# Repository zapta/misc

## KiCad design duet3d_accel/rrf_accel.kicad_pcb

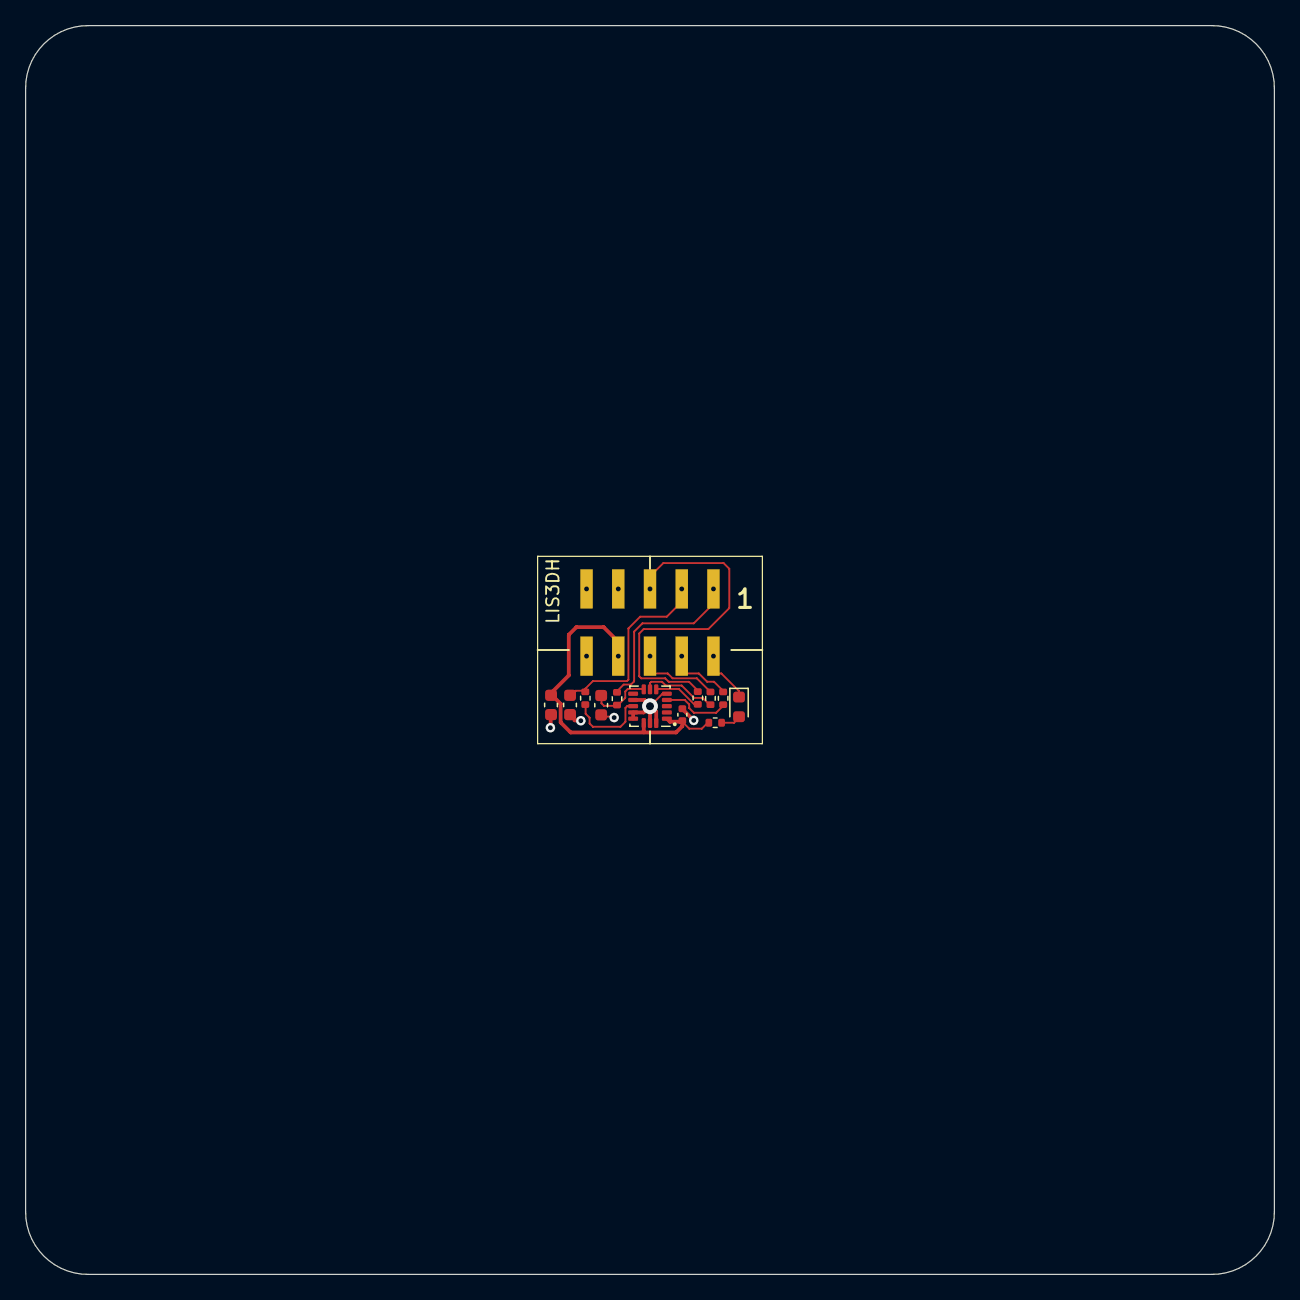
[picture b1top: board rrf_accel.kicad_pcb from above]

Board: 2 copper layers, 100.0 x 100.0 mm, 13 parts (0 on the bottom side), 13 nets.

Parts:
C1: 10uf; C_0603_1608Metric
C2: 100n; C_0402_1005Metric
C3, C4: 470pf; C_0603_1608Metric
D1: LED; LED_0603_1608Metric
J1: Conn_02x05_Odd_Even; PinHeader_2x05_P2.54mm_Vertical_SMD
R1, R2, R4, R5, R6: 62R; R_0402_1005Metric
R3: 220R; R_0402_1005Metric
U1: LIS3DH; LGA-16_3x3mm_P0.5mm_LayoutBorder3x5y

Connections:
+3V3: C1.1, C2.1, J1.8, R3.1, U1.1 (VDD_IO), U1.14 (VDD)
/CS: J1.1, R6.1
/INT: C3.1, J1.3, R1.1
/MISO: J1.6, R2.1
/MOSI: J1.5, R4.1
/SCK: J1.4, R5.1
GNDD: C1.2, C2.2, C3.2, C4.2, D1.1 (K), J1.2, U1.5 (GND), U1.10 (GND), U1.12 (GND), U1.13 (ADC3), U1.15 (ADC2), U1.16 (ADC1)
unnamed: D1.2 (A), R3.2
unnamed: C4.1, R6.2, U1.8 (CS)
unnamed: R1.2, U1.11 (INT1)
unnamed: R5.2, U1.4 (SCL/SPC)
unnamed: R4.2, U1.6 (SDA/SDI/SDO)
unnamed: R2.2, U1.7 (SDO/SA0)

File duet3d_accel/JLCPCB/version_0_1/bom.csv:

Designator,Footprint,Quantity,Value,LCSC Part #
C1,0603,1,10uf,C96446
C2,0402,1,100n,C1525
"C3, C4",0603,2,470pf,C1620
D1,0603,1,LED,C72043
J1,PinHeader_2x05_P2.54mm_Vertical_SMD,1,Conn_02x05_Odd_Even,C3294463
"R1, R2, R4, R5, R6",0402,5,62R,C25120
R3,0402,1,220R,C25091
U1,LGA-16_3x3mm_P0.5mm_LayoutBorder3x5y,1,LIS3DH,C15134

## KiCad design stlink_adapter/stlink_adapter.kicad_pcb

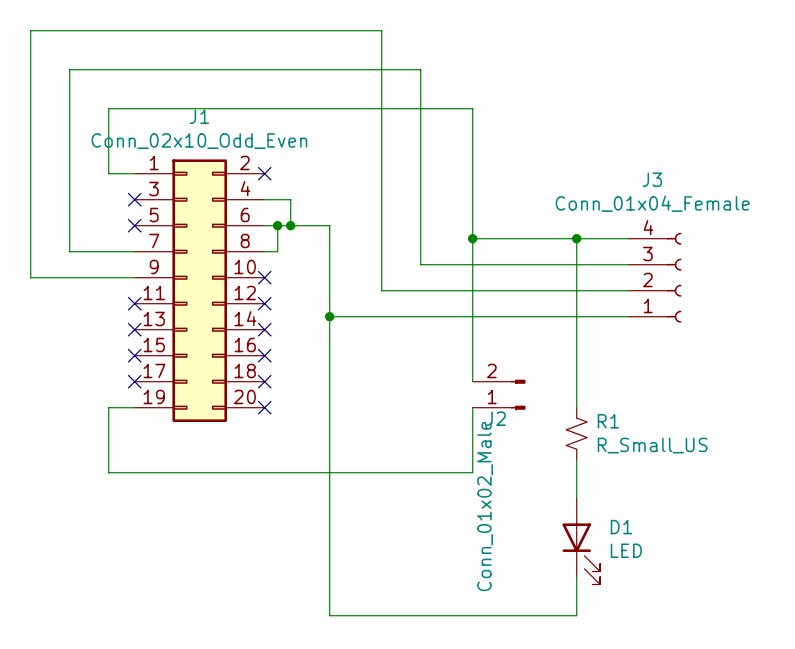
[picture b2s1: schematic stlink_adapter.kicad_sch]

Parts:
D1: LED; LED_0603_1608Metric_Pad1.05x0.95mm_HandSolder
J1: Conn_02x10_Odd_Even; PinHeader_2x10_P2.54mm_Vertical
J2: Conn_01x02_Male; PinHeader_1x02_P2.54mm_Vertical
J3: Conn_01x04_Female; PinHeader_1x04_P2.54mm_Vertical
R1: R_Small_US; R_0603_1608Metric_Pad1.05x0.95mm_HandSolder

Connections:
unnamed: D1.2 (A), R1.2
unnamed: D1.1 (K), J1.4, J1.6, J1.8, J3.1
unnamed: J1.1, J2.2, J3.4, R1.1
unnamed: J1.7, J3.3
unnamed: J1.9, J3.2
unnamed: J1.19, J2.1

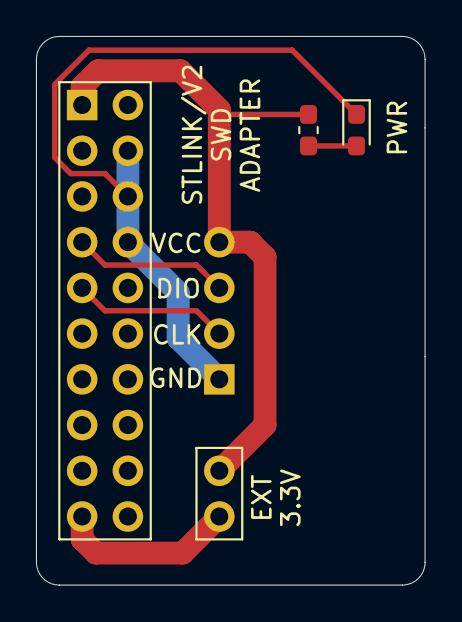
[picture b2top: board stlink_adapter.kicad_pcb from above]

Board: 2 copper layers, 21.6 x 30.5 mm, 5 parts (0 on the bottom side), 6 nets.

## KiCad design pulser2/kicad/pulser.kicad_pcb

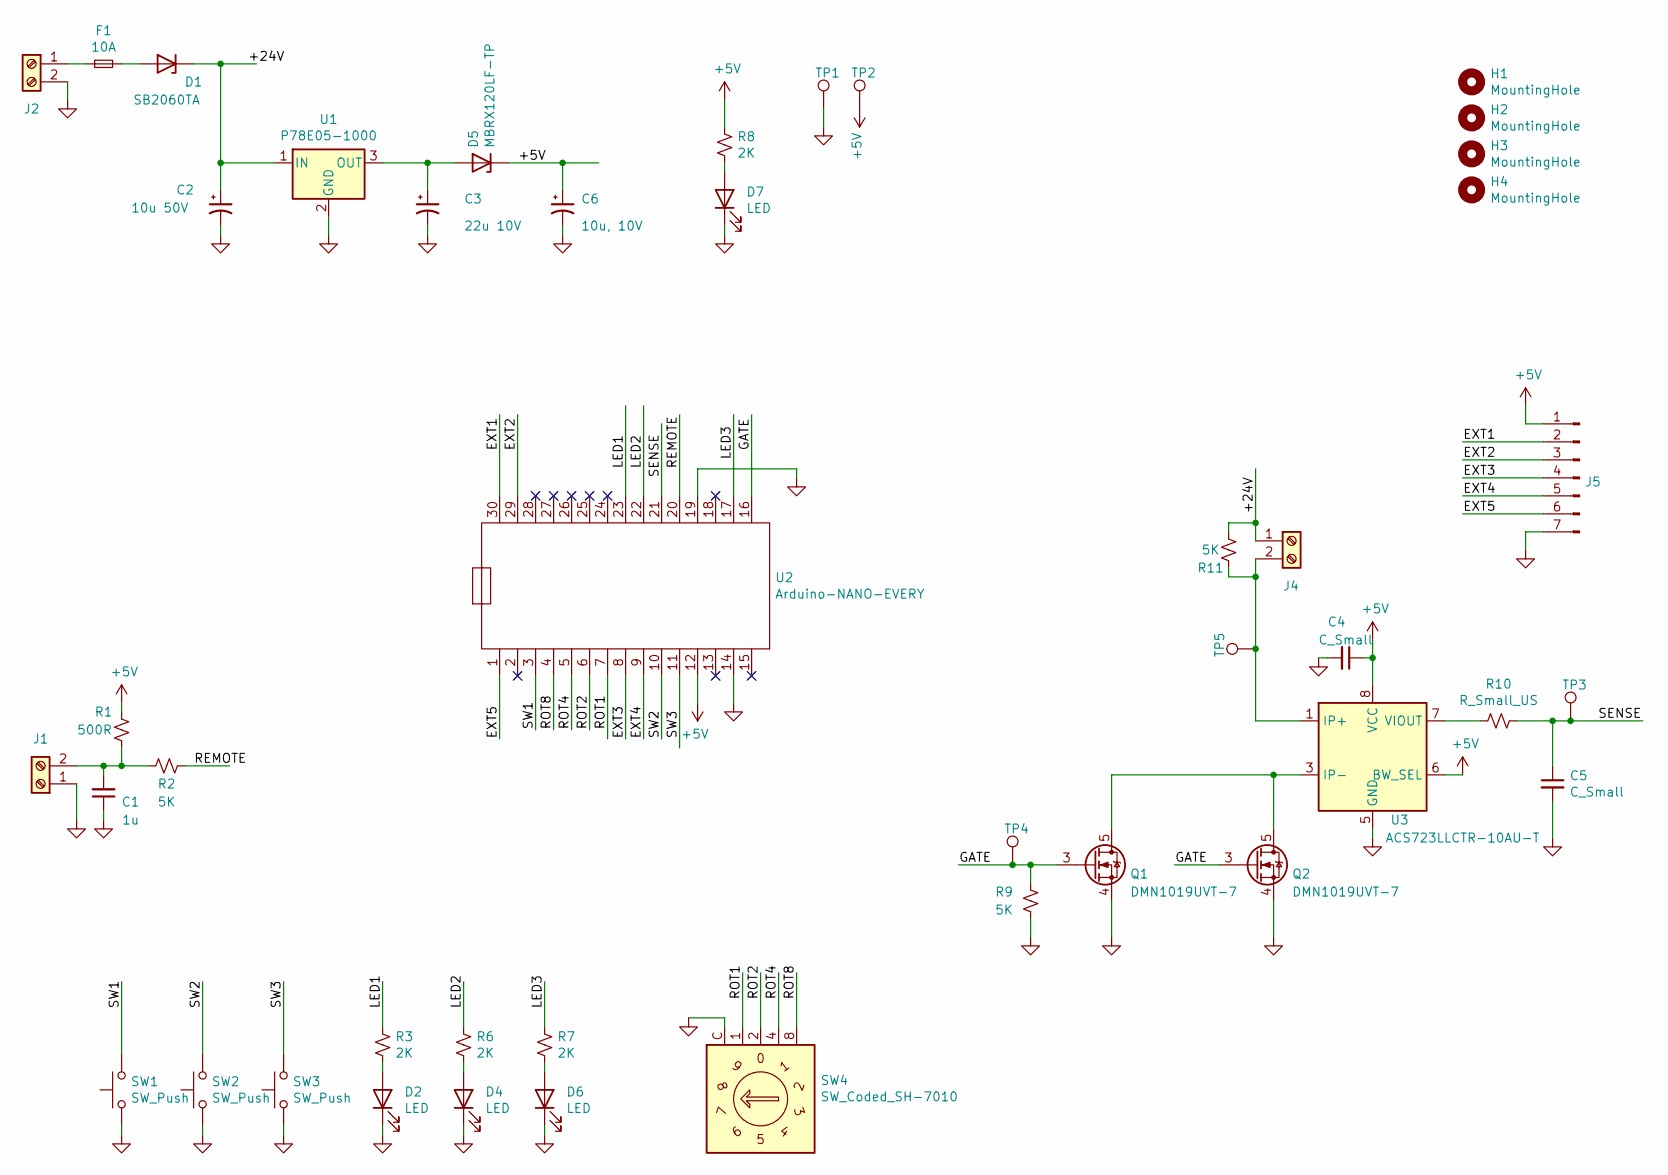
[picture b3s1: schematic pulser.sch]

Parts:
C1: 1u; C_0603_1608Metric
C2: 10u 50V; CP_Radial_D8.0mm_P2.50mm
C3: 22u 10V; CP_Radial_D5.0mm_P2.00mm
C4, C5: C_Small; C_0603_1608Metric
C6: 10u, 10V; C_1206_3216Metric_Pad1.42x1.75mm_HandSolder
D1: SB2060TA; D_DO-201AD_P12.70mm_Horizontal
D2, D4, D6, D7: LED; LED_0603_1608Metric
D5: MBRX120LF-TP; D_SOD-123
F1: 10A; Fuse_Blade_Mini_directSolder
H1, H2, H3, H4: MountingHole
J1: Screw_Terminal_01x02; TERMINAL_SMALL
J2, J4: Screw_Terminal_01x02; TerminalBlock_bornier-2_P5.08mm
J5: Conn_01x07_Male; Molex_KK-254_AE-6410-07A_1x07_P2.54mm_Vertical
Q1, Q2: DMN1019UVT-7; SOT-23-6_Handsoldering
R1: 500R; R_0603_1608Metric
R2, R9, R11: 5K; R_0603_1608Metric
R3, R6, R7, R8: 2K; R_0603_1608Metric
R10: R_Small_US; R_0603_1608Metric
SW1, SW2, SW3: SW_Push; SW_PUSH_6mm
SW4: SW_Coded_SH-7010; ROTARY2
TP1, TP2, TP3, TP4, TP5: TestPoint; Testpoint
U1: P78E05-1000; DC_DC
U2: Arduino-NANO-EVERY; NANO_33_Socket_Castell
U3: ACS723LLCTR-10AU-T; SOIC-8_3.9x4.9mm_P1.27mm

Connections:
+5V: C4.1, C6.1, D5.1 (K), J5.1, R1.2, R8.1, TP2.1, U2.12, U3.6 (BW_SEL), U3.8 (VCC)
/+24V: C2.1, D1.1 (K), J4.1, R11.2, U1.1 (IN)
/EXT1: J5.2, U2.30
/EXT2: J5.3, U2.29
/EXT3: J5.4, U2.8
/EXT4: J5.5, U2.9
/EXT5: J5.6, U2.1
/GATE: Q1.3 (G), Q2.3 (G), R9.2, TP4.1, U2.16
/LED1: R3.1, U2.23
/LED2: R6.1, U2.22
/LED3: R7.1, U2.17
/REMOTE: R2.2, U2.20
/ROT1: SW4.1, U2.7
/ROT2: SW4.2, U2.6
/ROT4: SW4.4, U2.5
/ROT8: SW4.8, U2.4
/SENSE: C5.1, R10.1, TP3.1, U2.21
/SW1: SW1.2, U2.3
/SW2: SW2.2, U2.10
/SW3: SW3.2, U2.11
GND: C1.1, C2.2, C3.2, C4.2, C5.2, C6.2, D2.1 (K), D4.1 (K), D6.1 (K), D7.1 (K), J1.1, J2.2, J5.7, Q1.4 (S), Q2.4 (S), R9.1, SW1.1, SW2.1, SW3.1, SW4.C, TP1.1, U1.2 (GND), U2.14, U2.19, U3.5 (GND)
unnamed: C1.2, J1.2, R1.1, R2.1
unnamed: C3.1, D5.2 (A), U1.3 (OUT)
unnamed: D1.2 (A), F1.2
unnamed: D2.2 (A), R3.2
unnamed: D4.2 (A), R6.2
unnamed: D6.2 (A), R7.2
unnamed: D7.2 (A), R8.2
unnamed: F1.1, J2.1
unnamed: J4.2, R11.1, TP5.1, U3.1 (IP+), U3.2 (IP+)
unnamed: Q1.1 (D), Q1.2 (D), Q1.5 (D), Q1.6 (D), Q2.1 (D), Q2.2 (D), Q2.5 (D), Q2.6 (D), U3.3 (IP-), U3.4 (IP-)
unnamed: R10.2, U3.7 (VIOUT)

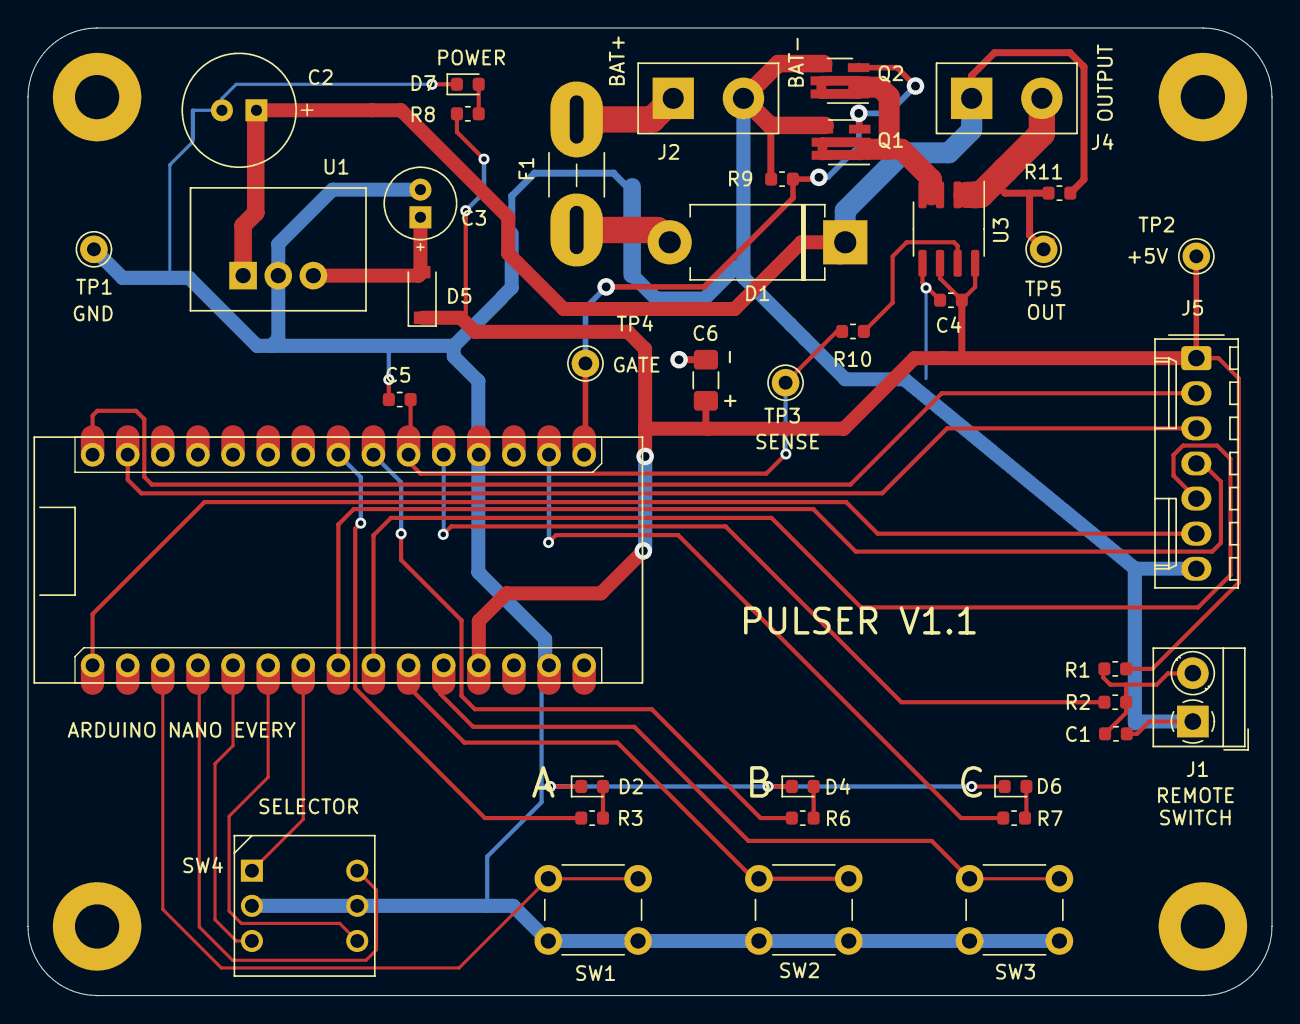
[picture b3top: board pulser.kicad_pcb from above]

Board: 2 copper layers, 90.0 x 70.0 mm, 44 parts (0 on the bottom side), 32 nets.

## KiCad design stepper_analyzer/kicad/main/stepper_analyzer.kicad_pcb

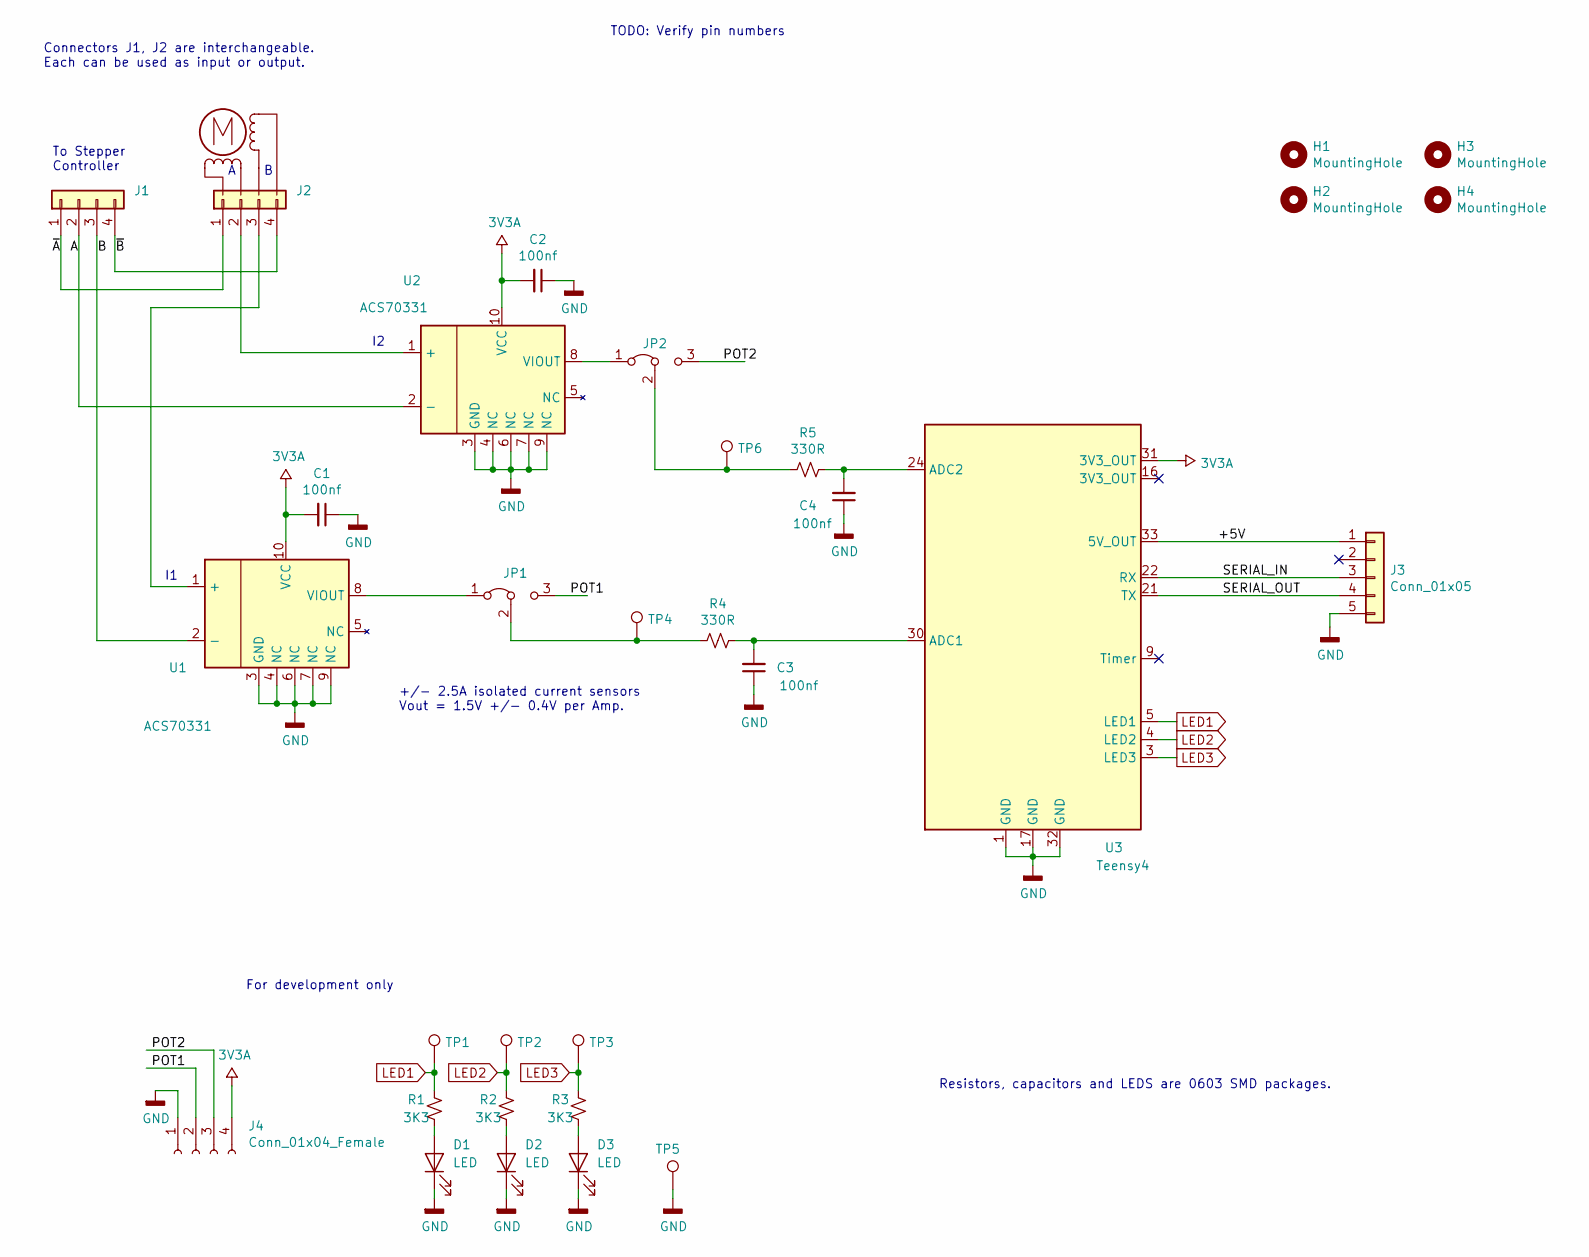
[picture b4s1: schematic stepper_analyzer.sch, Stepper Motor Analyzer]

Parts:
C1, C2, C3, C4: 100nf; C_0603_1608Metric
D1, D2, D3: LED; LED_0603_1608Metric
H1, H2, H3, H4: MountingHole; MountingHole_3.2mm_M3_Pad
J1, J2: Conn_01x04; Molex_KK-254_AE-6410-04A_1x04_P2.54mm_Vertical
J3: Conn_01x05; Molex_KK-254_AE-6410-05A_1x05_P2.54mm_Vertical
J4: Conn_01x04_Female; PinHeader_1x04_P2.54mm_Vertical
JP1, JP2: Jumper_3_Bridged12; PinHeader_1x03_P2.54mm_Vertical
M1: Stepper_Motor_bipolar
R1, R2, R3: 3K3; R_0603_1608Metric
R4, R5: 330R; R_0603_1608Metric
TP1, TP2, TP3, TP4, TP5, TP6: TestPoint; TestPoint_Loop_D1.80mm_Drill1.0mm_Beaded
U1, U2: ACS70331; Allegro_QFN-12-10-1EP_3x3mm_P0.5mm
U3: Teensy4; TEENSY40

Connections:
+3V3A: C1.2, C2.2, J4.4, U1.10 (VCC), U2.10 (VCC), U3.31 (3V3_OUT)
/+5V: J3.1, U3.33 (5V_OUT)
/A: J1.2, U2.2 (-)
/B: J1.3, U1.2 (-)
/POT1: J4.2, JP1.3 (B)
/POT2: J4.3, JP2.3 (B)
/SERIAL_IN: J3.3, U3.22 (RX)
/SERIAL_OUT: J3.4, U3.21 (TX)
/~A: J1.1, J2.1
/~B: J1.4, J2.4
GNDD: C1.1, C2.1, C3.1, C4.1, D1.1 (K), D2.1 (K), D3.1 (K), J3.5, J4.1, TP5.1, U1.3 (GND), U1.4 (NC), U1.6 (NC), U1.7 (NC), U1.9 (NC), U2.3 (GND), U2.4 (NC), U2.6 (NC), U2.7 (NC), U2.9 (NC), U3.1 (GND), U3.17 (GND), U3.32 (GND)
LED1: R1.1, TP1.1, U3.5 (LED1)
LED2: R2.1, TP2.1, U3.4 (LED2)
LED3: R3.1, TP3.1, U3.3 (LED3)
unnamed: C3.2, R4.1, U3.30 (ADC1)
unnamed: C4.2, R5.1, U3.24 (ADC2)
unnamed: D1.2 (A), R1.2
unnamed: D2.2 (A), R2.2
unnamed: D3.2 (A), R3.2
unnamed: J2.2, U2.1 (+)
unnamed: J2.3, U1.1 (+)
unnamed: JP1.1 (A), U1.8 (VIOUT)
unnamed: JP1.2 (C), R4.2, TP4.1
unnamed: JP2.1 (A), U2.8 (VIOUT)
unnamed: JP2.2 (C), R5.2, TP6.1

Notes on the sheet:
TODO: Verify pin numbers
To Stepper Controller
Connectors J1, J2 are interchangeable. Each can be used as input or output.
Resistors, capacitors and LEDS are 0603 SMD packages.
+/- 2.5A isolated current sensors Vout = 1.5V +/- 0.4V per Amp.
For development only

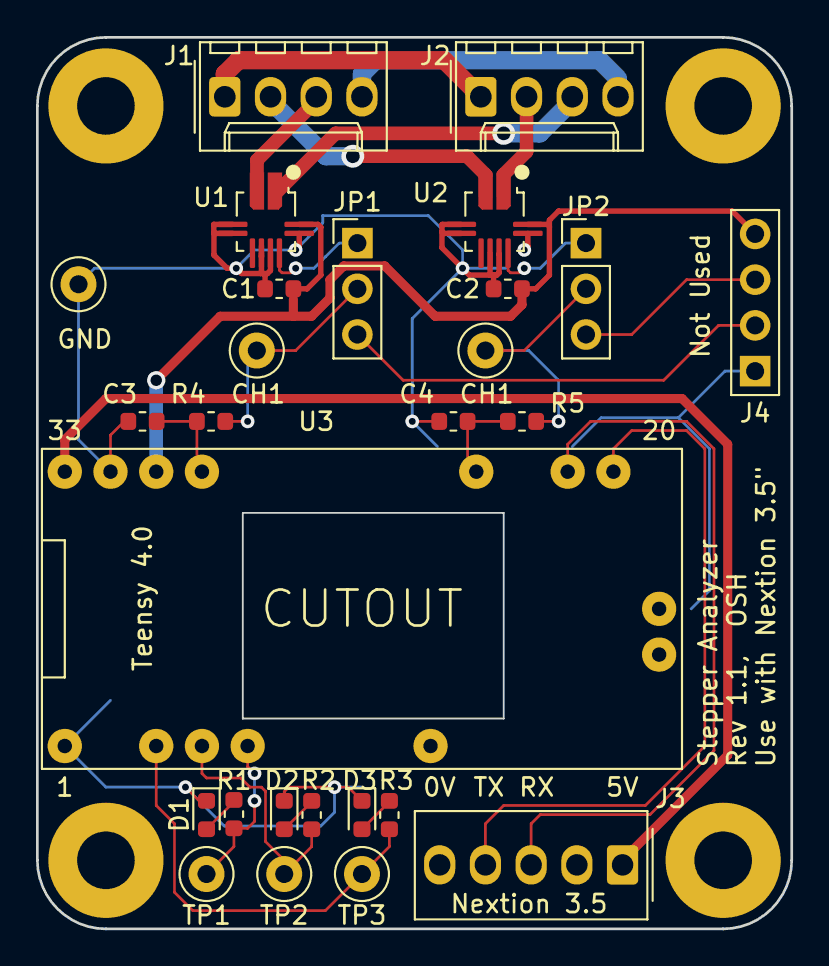
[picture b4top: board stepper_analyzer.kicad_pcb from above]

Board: 2 copper layers, 41.9 x 49.5 mm, 31 parts (0 on the bottom side), 25 nets.

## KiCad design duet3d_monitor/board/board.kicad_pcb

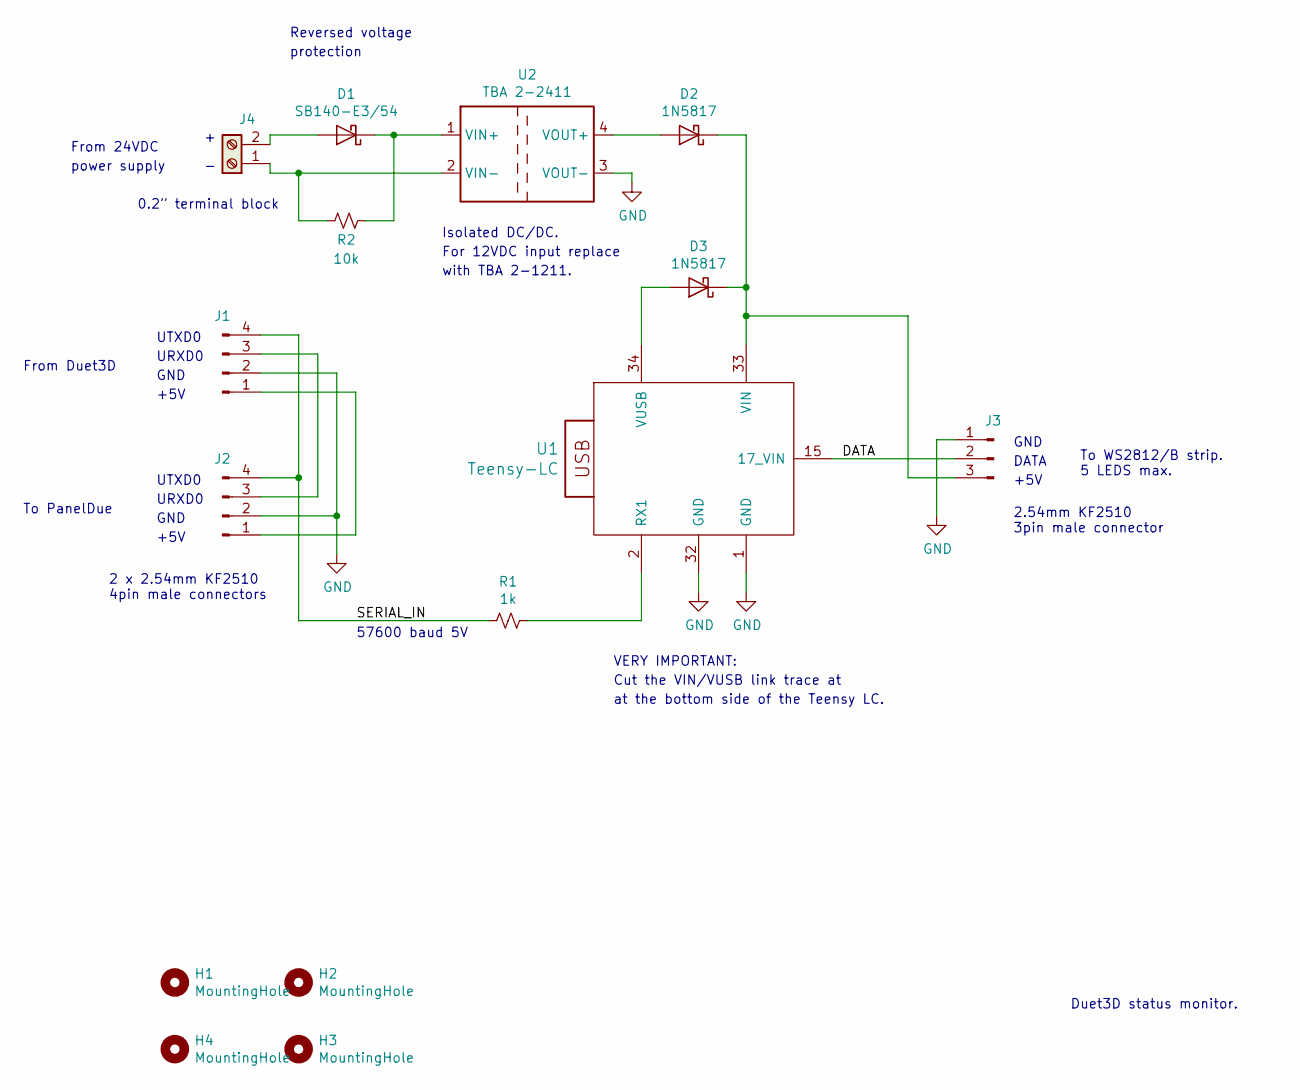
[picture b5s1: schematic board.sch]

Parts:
D1: SB140-E3/54; Diode
D2, D3: 1N5817; Diode
H1, H2, H3, H4: MountingHole; Mounting-hole
J1, J2: Connector_01x04_Male; Connector_4
J3: Connector_01x03_Male; Connector_3
J4: Screw_Terminal_x02; Terminal-block
R1: 1k; Resistor
R2: 10k; Resistor
U1: Teensy-LC; TEENSY-LC
U2: TBA 2-2411; DC-DC

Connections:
/DATA: J3.2, U1.15 (17_VIN)
/SERIAL_IN: J1.4, J2.4, R1.1
GND: J1.2, J2.2, J3.1, U1.1 (GND), U1.32 (GND), U2.3 (VOUT-)
unnamed: D1.A, J4.2
unnamed: D1.K, R2.2, U2.1 (VIN+)
unnamed: D2.A, U2.4 (VOUT+)
unnamed: D2.K, D3.K, J3.3, U1.33 (VIN)
unnamed: D3.A, U1.34 (VUSB)
unnamed: J1.1, J2.1
unnamed: J1.3, J2.3
unnamed: J4.1, R2.1, U2.2 (VIN-)
unnamed: R1.2, U1.2 (RX1)

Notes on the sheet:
For 12VDC input replace
with TBA 2-1211.
To WS2812/B strip. 5 LEDS max.
VERY IMPORTANT:
To PanelDue
Cut the VIN/VUSB link trace at
at the bottom side of the Teensy LC.
Reversed voltage
protection
From Duet3D
From 24VDC
power supply
57600 baud 5V
Isolated DC/DC.
Duet3D status monitor.
+5V
GND
URXD0
UTXD0
DATA
2 x 2.54mm KF2510 4pin male connectors
2.54mm KF2510 3pin male connector
0.2” terminal block

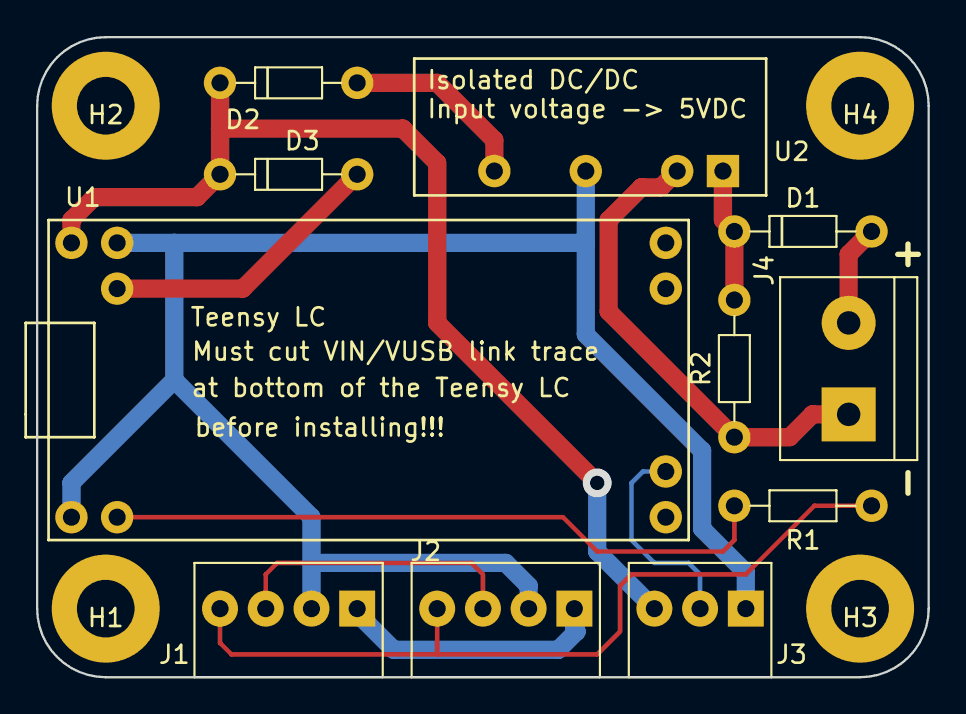
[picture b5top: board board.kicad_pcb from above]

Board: 2 copper layers, 49.5 x 35.6 mm, 15 parts (0 on the bottom side), 12 nets.

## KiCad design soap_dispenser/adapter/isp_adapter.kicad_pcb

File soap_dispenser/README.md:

Running Arduino firmware on a GOJO LTX-7 Soap Dispenser 
============

This project documents how I modified our GOJO LTX-7 soap dispenser by reflashing it
 with an Arduino firmware. 

Apparently the GOJO LTX-7 and possibly similar models are Arduino ready. They are powered by 
AVR Tiny48 (256B RAM, 4K FLASH) and have row of PCB pads that provide access to the 
ISP signals for programming.

IMPORTANT: once you reflash your soap dispenser you cannot restore the original firmware. 
If you want to be able to restore the original firmware, replace the ATTiny48 
on the board with a digikey ATTINY48-MURCT-ND IC and install the stock IC 
back to restore the original functionality.

To reflash the soap dispenser I soldered a row of header pins that connects via an 
adapter board to an Arduino supported programmer (the one I used in Atmel MKII).  
The arduino sketch I programmed is minimal but sufficient for our needs. It doesn't 
performed some of the advanced functions of the stock firmware such as current and 
voltage sensing, RFID, etc and just performs a basic functionality of activating the 
pump motor each trigger it gets from the IR proximity sensors.  To do that it needs to 
sense the motor position switch to stop the motor when reaching that 'parking' angle 
and it controls the motor via 4 power mosfets in H configuration. The sketch uses 
only 3 of the H bridge modes (motor off, forward, forced brake) and doesn't use the 
reverse mode. The number of pump strokes (each a single motor revolution) is software 
programmable, the stock devices are programmed for a single stroke, we prefer two 
strokes per activation for extra soap. The Arduino sketch also puts the MCU to 
sleep between activations to reduce the power consumption.

The Arduino sketch uses the ATTiny48 Core by Spence Konda https://github.com/SpenceKonde/ATTinyCore 
which also sells AVR Tiny boards on Tindie in case you want to do some independent 
ATTiny development (the boards are not required to run Arduino sketches on the GOJO soap dispenser). 
You will need to install the ATTIny48 Core in your Arduino IDE to be able to compile the 
Arduino sketch. The IDE setting uses is documented at the top of the Arduino sketch.

Content of this repository
* Partial Kicad schematic of the board. It's sufficient to understand how to interface 
with the sensors and control the motor. https://github.com/zapta/misc/tree/master/soap_dispenser/board
* Arduino sketch with simple but useful soap dispensing logic.  
https://github.com/zapta/misc/tree/master/soap_dispenser/arduino
* Kicad schematic and gerbers for a  an ISP adapter board. This is not 
really necessary and it's faster to just hack one from a small prototyping PCB. 
https://github.com/zapta/misc/tree/master/soap_dispenser/adapter

The soap dispencer electronic board. The ICSP programming signals are at the 8 pad row at the top of the board.

<br>

To remove the mechanism (the black unit in the picture), press down the two tabs above 
it, push the mechanism up a little bit to release it and then pull it toward you.

<br>

To access the electronic board you first need to release the motor fork that activate the 
pump. Press in at the two points marked with an arror and seperate the motore fork 
from the carriage that moves up and down.

<br>

Then, remove the screw (1), desolder the red (2) and black (3) wires from the battery tabs, 
press and release the tab (4) and pull up the motor and the white assmebly (5). the 
unit with the motor and electronic board will come out.

<br>

To program the unit from the Arduino IDE you need to connect the programmer signals 
to the raw of 8 pads at the top (only 6 pins are used). Check the schematic here for 
exact pads to use. I chose to solder a 90 degrees 8 pin header which provide easy 
access to the programing pad and has enough clearance when reassembling the soap
dispenser for eazy future modfications.

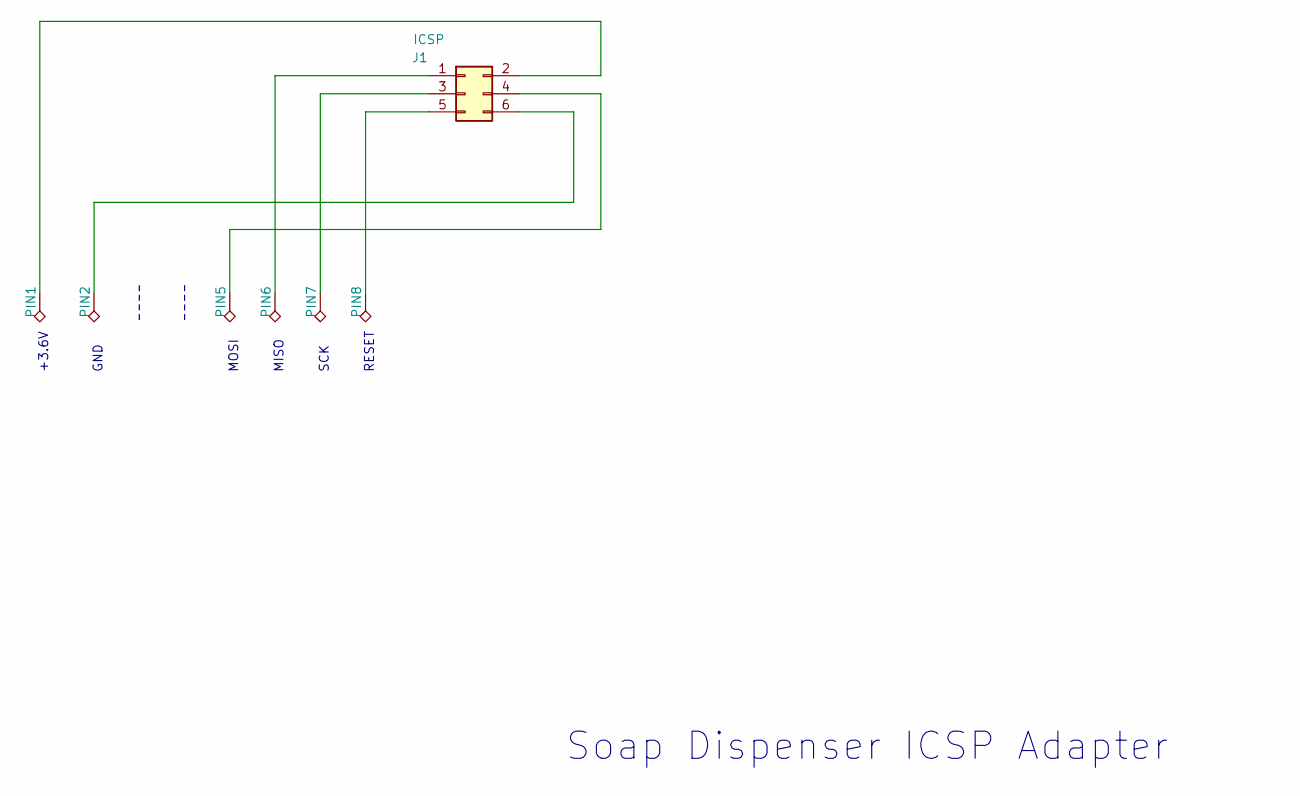
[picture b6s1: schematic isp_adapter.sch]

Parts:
J1: ICSP; Pin_Header_Straight_2x03_Pitch2.54mm
PIN1, PIN2, PIN5, PIN6, PIN7, PIN8: pogo_pin; pogo_horizontal

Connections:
unnamed: J1.1, PIN6.1
unnamed: J1.2, PIN1.1
unnamed: J1.3, PIN7.1
unnamed: J1.4, PIN5.1
unnamed: J1.5, PIN8.1
unnamed: J1.6, PIN2.1

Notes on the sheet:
+3.6V
GND
MOSI
MISO
SCK
RESET
Soap Dispenser ICSP Adapter

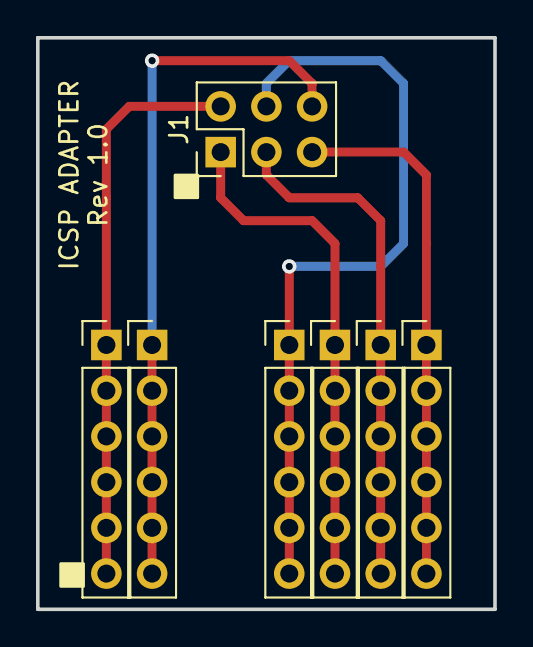
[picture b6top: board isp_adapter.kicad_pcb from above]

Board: 2 copper layers, 25.4 x 31.8 mm, 7 parts (0 on the bottom side), 6 nets.

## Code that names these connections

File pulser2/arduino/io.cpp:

#include <arduino.h>
#include "io.h"

namespace io {

// LEDs. Active high.
DigitalOutPin LED0(PORTE, 2, 1);
DigitalOutPin LED1(PORTB, 2, 1);
DigitalOutPin LED2(PORTC, 6, 1);
DigitalOutPin LED3(PORTC, 5, 1);

// MOSFET gate output. Active high.
DigitalOutPin GATE(PORTC, 4, 1);

// Current sense input.
AnalogInPin CURRENT_SENSE(15);

// Rotary inputs. Active low.
static DigitalInPin ROT1(PORTD, 0, 0);
static DigitalInPin ROT2(PORTD, 1, 0);
static DigitalInPin ROT4(PORTD, 2, 0);
static DigitalInPin ROT8(PORTD, 3, 0);

// Remote switch. Active low.
DigitalInPin REMOTE_SWITCH(PORTA, 0, 0);

int rotary_read() {
  int value = 0;
  value +=  ROT1.is_on() ? 1 :0;
  value +=  ROT2.is_on() ? 2 :0;
  value +=  ROT4.is_on() ? 4 :0;
  value +=  ROT8.is_on() ? 8 :0;
  return value;
}

// USB serial printf.
static char buffer[200];

void printf(const char* format, ...) {
  va_list argptr;
  va_start(argptr, format);
  vsnprintf(buffer, sizeof(buffer), format, argptr);
  Serial.print(buffer);
  va_end(argptr);
}


int AnalogInPin::read() {
  // Select input
  ADC0.MUXPOS = ain_;

  // Single reading. No accomulation.
  ADC0.CTRLB = 0;

  // Ref = VDD, Capacitance, clock /16
  ADC0.CTRLC = 0x53;

  // Start a conversion.
  ADC0.COMMAND = ADC_STCONV_bm;

  // Wait for conversion done.
  while (!(ADC0.INTFLAGS & ADC_RESRDY_bm)) {};

  // Read the 16 bit value with interrupts disabled.
  const  uint8_t status = SREG;
  cli();
  const uint8_t low = ADC0.RESL;
  const uint8_t high = ADC0.RESH;
  SREG = status;

  // Combine and return.
  return (high << 8) | low;
}

void dump_adc0_registers() {
  io::printf("ADC0:\n");
  io::printf("  CTRLA:    0x%02x\n", ADC0.CTRLA);
  io::printf("  CTRLB:    0x%02x\n", ADC0.CTRLB);
  io::printf("  CTRLC:    0x%02x\n", ADC0.CTRLC);
  io::printf("  CTRLD:    0x%02x\n", ADC0.CTRLD);
  io::printf("  CTRLE:    0x%02x\n", ADC0.CTRLE);
  io::printf("  SAMPCTRL: 0x%02x\n", ADC0.SAMPCTRL);
  io::printf("  MUXPOS:   0x%02x\n", ADC0.MUXPOS);
  io::printf("  COMMAND:  0x%02x\n", ADC0.COMMAND);
  io::printf("  EVCTRL:   0x%02x\n", ADC0.EVCTRL);
}

}  // namespace io

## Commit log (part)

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2015-10-05 Changed the board placement and rerouted (moved USB connector up) and push butto to the center.
2015-10-06 Tweaked the design, updated the BOM.
2015-10-10 Minor tweak of the top silk layer.
2015-10-10 Generated gerbers and PDFs.
2015-11-17 Added Readme file
2016-03-17 Work in progress
2016-03-20 Work in progress.
2016-03-21 Work in progress. Second printed prototype.
2016-03-25 Before printing prototype #3.
2016-03-27 More tweaks. This is the version of proto #5 (white).
2016-03-29 Final
2016-04-14 Work in proegress.
2016-04-15 Minor tweak
2016-06-19 Added comments to the uploader
2016-06-19 Updated flashair script for Simplify3D 3.1.0 which has a differnet behavior with the x3g post processing script.
2016-08-14 First version of the cube puzzle.
2016-08-16 Stable version.
2016-08-18 Checking in Flash Forge Creator Pro spool hanger.
2016-08-18 Increased eps1 for cleaner rendering.
2016-08-20 A stable version of spool shaft. Also renamed a few files.
2016-08-20 Minor cleanup
2016-08-24 Added a side slot to the end pieces.
2016-08-24 Converted to metric design.
2016-08-24 Added oled mount pins.
2016-08-25 Added curl connection timeout and failure detection.
2016-08-25 Reduced the center of gravity for better stability.
2016-09-30 Added Sparkfun eagle cam files (2 layers). Also good for pcbway.
2016-10-24 First version of a script file to deleted all x3g files on the flashair drive.
2016-10-24 Added TODO comment.
2016-10-26 Added interactive per file deletion approval.
2016-12-28 First version that was tested on car.
2016-12-30 Initial layout completed.
2016-12-31 Ready for final routing.
2016-12-31 Removed TODO from schematic.
2017-01-01 A few tweaks before final auto routing.
2017-01-01 Performed final auto routing.
2017-01-01 Tweaked voltage output labels.
2017-01-02 Added first draft of an enclosure.
2017-01-02 Recent 3D designs
2017-01-02 Pending open 3D files.
2017-01-02 BOM work in progress.
2017-01-02 Fixed library exporter for eagle v7.
2017-01-02 Completed BOM. Generated library from schematic file.
2017-01-02 Added a basic readme file.
2017-01-02 Renamed cutoff directory to battery_cutoff
2017-01-02 Completed the case design.
2017-01-02 Updated readme file.
2017-01-02 Minor naming tweak.
2017-01-02 Minor variable renaming.
2017-01-19 Updated files for actual V1 built.
2017-03-13 Checkin in various modified 3d models
2017-06-16 Tweaked S3D wifi upload file.
2017-06-18 Stable plots.
2017-06-18 Additional cleanup
2017-06-18 Deleted test file.
2017-07-02 Flashforge carrige led holder
2018-03-02 Simplify 3D profile
2018-03-02 Submitting all open 3d files.
2018-03-02 Removed obsolete files.
2018-03-09 Updated ring.com wedge model
2018-12-10 Added initial kicad schema
2018-12-10 Minor schema tweaks.
2018-12-10 Deleted kicad backup files.
2018-12-10 Updated .gitignore to ignore kicad's backup files.
2018-12-11 Renamed capture directory to resources
2018-12-11 Renamed kicad directory
2018-12-11 Added PCB for ICSP adapter.
2018-12-12 Minor schema cleanup
2018-12-14 First draft of squeeze cycle implementation.
2018-12-14 First working version. Still a bunch of TODOs.
2018-12-14 Added a comment with current sense resistor package size.
2018-12-14 Added sleep mode.
2018-12-15 Added a skeleton README
2018-12-15 Now dispensing only when door is closed.
2018-12-17 Changed the number of strokes per activation from 1 to two (more soap). Also minor cleanups.
2018-12-17 Added pictures.
2019-01-11 Submitting original files.
2019-01-24 Snapshot of Simplify3d profile used to print PETG parts.
2019-01-24 Updated Simplify3d profile
2019-03-10 Initial duet config
2019-03-17 Tweaked duet configuration.
2019-03-17 Stable homing using endstops
2019-03-19 Changes endstops to stall detection. Added bed leveling macro.
2019-03-19 Tweaked bed dimensions
2019-03-21 Config tweaks
2019-03-24 Added BLTouch breakout PCB.
2019-03-30 Updated scripts.
2019-04-19 Working Simplify3d configuration.
2019-04-19 PETG specific simplify3d profile
2019-05-24 Initial duet monitor files
2019-05-25 A working version with rgb led.
2019-05-25 Minor led tweaks.
2019-05-25 Renamed .hpp files .h for consistency.
2019-06-01 Latest changes.
2019-06-01 LED box
2019-06-07 Created kicad project
2019-06-07 Minor tweaks
2019-06-08 Added screenshot of layout
2019-06-08 Updated schematic snapshot
2019-06-09 Ready for submission.
2019-06-11 Added yellos status color for cooling
2019-06-13 Minor schematic tweaks
2019-06-13 Regenerated net list
2019-06-23 Snapshot of slic3r pe
2019-07-20 Flushing duet/sys and duet/macros
2019-08-06 Renamed slic3r_pe to slicer_prusa
2019-08-06 Updated prusa slicer config (with TPU)
2019-08-06 Pending changes.
2019-09-02 Downloaded version.
2019-09-05 Pressure advance
2019-09-14 Flushing hevo changes.
2019-09-14 Flushing changes under 3d/
2019-09-17 First installment of the stepper analyzer firmware.
2019-09-28 Added original TFT graphics files.
2019-09-28 First version with working display.
2019-09-30 Now sampling on timer2 ticks @50kps
2019-10-01 Migrated to T4.
2019-10-04 Refactored into a few modules
2019-10-05 Flushing current state.
2019-10-09 Fluhing latest changes.
2019-10-10 All four screen are working
2019-10-10 Update arduino.ino
    Test
2019-10-10 Added ADC library
    Added temporary Teensy 4.0 ADC files. Downloaded from https://forum.pjrc.com/threads/57860-T4-ADC-Library-V0
2019-10-30 Generated gerbers
2019-10-30 Sent PCB to fabrication.
2019-11-01 Flushing changes before zesty.
2019-11-27 Now forcing color updates to the LEDS every few seconds.
2020-01-30 First version of the duet parser.
2020-01-30 Cleaed up directory structure.
2020-01-30 First working version.
2020-02-01 Work in progress. Functional but crude.
2020-02-02 Added code to read config from SD card.
2020-02-02 More cleanup and tweaking.
2020-02-02 Minor tweaks and cleanup.
2020-02-02 Various UI tweaks.
2020-02-04 Changed the config file to have full url rather than just IP.
2020-02-04 Refactored string conversion functions.
2020-02-05 Working on burn script.
2020-02-06 Organized the win burner.
2020-02-07 Cleaned up commented out commands.
2020-02-07 Sync'ed changes from slicer.
2020-03-09 Regular update.
2020-05-12 Cleaned up. First running version.
2020-05-12 Flushing SD card state.
2020-05-13 Some code cleanup. Added TODOs.
2020-05-13 Added credits for the original author.
2020-05-14 Added command line flags.
2020-05-15 Minor tweaks. Added flags for layer markers.
2020-05-16 Rename directory from duet_automesh to duet3d_automesh.
2020-05-17 Tweaks.
2020-05-30 Now alowing negtive --meshable coordinates.
2020-06-14 Changed the gcode parsing to consider also negative x,y values.
2020-06-21 Submitting all changes before switching to the Nextion aproach.
2020-06-23 Before transitioning to StaticString class.
2020-06-27 Minor notification tweak.
2020-07-06 Deleted unused filed.
2020-07-11 Generated gerbers.
2020-07-19 Assorted tweaks. Work in progress.
2020-07-24 stepper analyzer files were moved to an independent github repository.
2020-08-01 XYZ homing functioning. (single Z driver)
2020-08-01 Added command to enable camera click. (still doesn't work)
2020-08-01 Camera clicks works now.
2020-08-29 Flushing all pending changes.
2020-08-29 Initial version of a timer + adc.
2020-08-30 Added reading of adc2.
2020-08-30 Regenerated code with per-perppheral files.
2020-09-05 First version.
2020-09-05 Cleaned up and generted ground plane.
2020-09-05 Narrower fuse slot. Also regenerated gerbers.
2020-09-05 Generated schematic PDF.
2020-09-06 Added stlink v2 swd adapter.
2020-09-06 Tweaked and generated gerbers.
2020-09-10 Added pulser version for arduino nano every.
2020-09-11 Final verstion. Ordered as V1.1.
2020-09-11 Added skeleton for program selections.
2020-09-12 Added basic i/o.
2020-09-12 Added Arduino Nano Every MCU datasheet.
2020-09-24 Downloaded fusion 360 designs before the license restrictions.
2020-09-26 Added cubemx stm32401. Only a single DMA cycle is triggered.
2020-09-26 Changed the DMA buffer from 32 bit to 16 bit items.
2020-11-28 Flush changes
2020-11-28 Deleted obsolete files.
2020-11-28 Deleted large 3d files.
2020-12-19 Cleaned up old stm32 cube files.
2020-12-20 stm32401: moved LED outputs, added SPI.
2020-12-21 Cloned a new stm32f401_2 directory.
2020-12-22 Flushing cube mx changes.
2020-12-22 Renamed stm32f401_2 back to stm32f401
2021-01-08 Regenerated the source files as a baseline for next change.
2021-01-08 Moved leds 1,2,3 away from port b.
2021-01-08 Moved RST pin off port b.
2021-01-08 Added definitions of output pins TFT_D8-15.
2021-01-23 Flushing latest version.
2021-01-27 Updated pins for new PCB
2021-05-16 Miniware MHP30 heater manual backup.
2021-05-16 Exported the PDF in a compressed format.
2022-04-22 fix typo 'reassmebling' to 'reassembling'
2022-11-16 Added random generator script
2023-01-09 working. 2 chan.
2023-01-15 Tweaked platformio.ini
2023-01-15 Virgin arduino esp32 project
2023-01-29 Clean new project.
2023-01-29 Copied scan/response test.
2023-02-12 Removed esp32 example.
2023-03-15 Initial version of React test.
2023-03-16 Before Apex Charts
2023-03-16 Static apex graph
2023-04-22 initial check in of a test project.
2023-04-30 Added serial test
2023-04-30 Added serial test for linux
2023-05-01 Refactored
2023-05-01 Added rx tasks.
2023-05-02 Simplify task names.
2023-05-02 Changed the command callback to be async
2023-05-03 Cleaned up logging.
2023-05-03 Added .gitignore
2023-05-10 Added a new mxcube project
2023-05-11 Added pio project
2023-05-27 Added a clean weact smt32h750 arduino project.
2023-05-27 Removed a redundant directory.
2023-07-10 Bump tough-cookie from 4.1.2 to 4.1.3 in /react/hello-world
    Bumps [tough-cookie](https://github.com/salesforce/tough-cookie) from 4.1.2 to 4.1.3.
    - [Release notes](https://github.com/salesforce/tough-cookie/releases)
    - [Changelog](https://github.com/salesforce/tough-cookie/blob/master/CHANGELOG.md)
    - [Commits](https://github.com/salesforce/tough-cookie/compare/v4.1.2...v4.1.3)
    ---
    updated-dependencies:
2023-07-13 Bump semver from 6.3.0 to 6.3.1 in /react/hello-world
    Bumps [semver](https://github.com/npm/node-semver) from 6.3.0 to 6.3.1.
    - [Release notes](https://github.com/npm/node-semver/releases)
    - [Changelog](https://github.com/npm/node-semver/blob/v6.3.1/CHANGELOG.md)
    - [Commits](https://github.com/npm/node-semver/compare/v6.3.0...v6.3.1)
    ---
    updated-dependencies:
2023-07-20 Bump word-wrap from 1.2.3 to 1.2.4 in /react/hello-world
    Bumps [word-wrap](https://github.com/jonschlinkert/word-wrap) from 1.2.3 to 1.2.4.
    - [Release notes](https://github.com/jonschlinkert/word-wrap/releases)
    - [Commits](https://github.com/jonschlinkert/word-wrap/compare/1.2.3...1.2.4)
    ---
    updated-dependencies:
    - dependency-name: word-wrap
2023-08-30 Bump @adobe/css-tools from 4.2.0 to 4.3.1 in /react/hello-world
    Bumps [@adobe/css-tools](https://github.com/adobe/css-tools) from 4.2.0 to 4.3.1.
    - [Changelog](https://github.com/adobe/css-tools/blob/main/History.md)
    - [Commits](https://github.com/adobe/css-tools/commits)
    ---
    updated-dependencies:
    - dependency-name: "@adobe/css-tools"
2023-09-23 First layout.
2023-09-24 Layout in progress.
2023-09-24 More layout.
2023-09-24 Renamed libraries
2023-09-24 Fixed schematic.
2023-09-25 Tweaked schematic and layout.
2023-09-27 Updated .gitignore.
2023-11-07 Updated schematic.
2023-11-18 Added sot23-5 smd adapter
2023-11-18 Created adapter panel (5 x 5)
2023-11-19 Completed the layout of the smd adapters (5 kinds)
2023-11-20 Added export of chrome context search plugin.
2023-11-20 Deleted a backup file.
2023-11-23 Added a directory for green pak experimentation.
2023-11-24 More progress with the SPI greenpak.
2023-11-24 More progress on the spi mux.
2023-11-24 Updated the greenpak design
2023-11-24 Added to the greenpack SPI design a MISO path.
2023-11-24 Fixed name of context search plugin directory
2023-11-24 More progress on the spi design.
2023-11-24 Updated the spi greenpak design.
2023-11-25 Cleaned up spi mux 01.
2023-11-25 Minimalist variant 02 is now working.
2023-12-25 Added a test kicad project to test paneling.
2024-01-24 Updated context search settings.
2024-07-28 Added nir test discord script.
2024-07-29 Reorginized the lcd1602 example
2024-07-29 Display example works.
2024-09-21 Skeleton of configobj test
2025-02-28 Added skeleton for lsftdi.py
2025-05-14 Changed from slices to starts.
